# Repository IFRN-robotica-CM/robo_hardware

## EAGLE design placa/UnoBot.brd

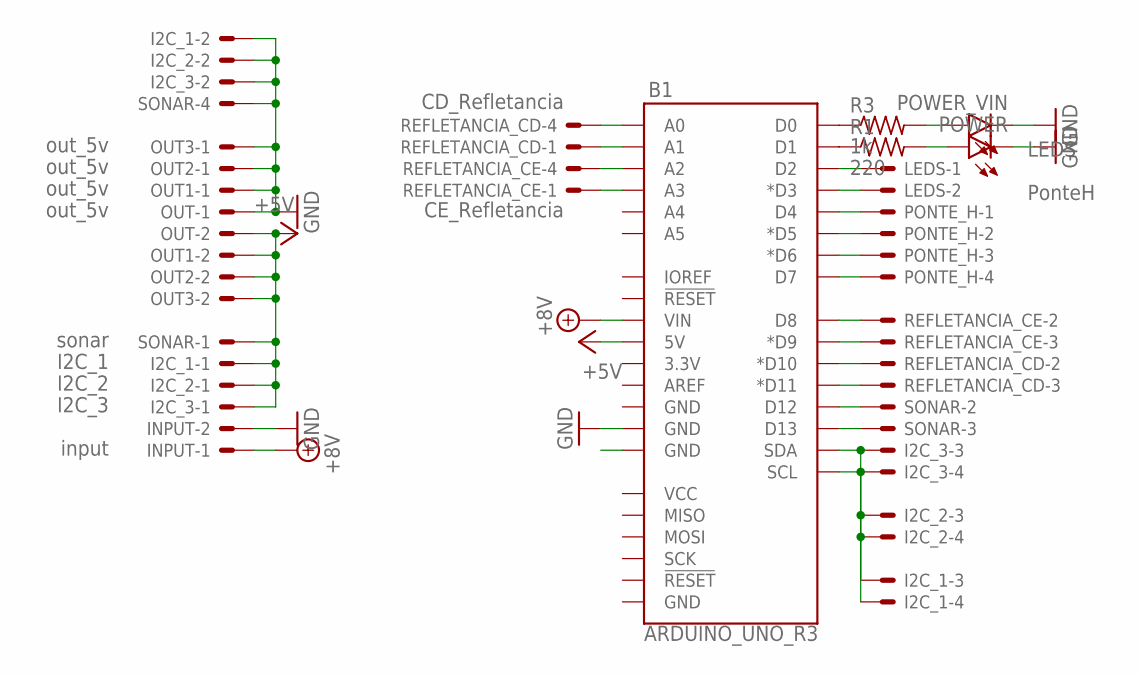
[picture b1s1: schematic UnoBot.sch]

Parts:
B1: ARDUINO_UNO_R3; ARDUINO_R3
I2C_1: I2C_1; JST-XH-04-PACKAGE-LONG-PAD
I2C_2: I2C_2; JST-XH-04-PACKAGE-LONG-PAD
I2C_3: I2C_3; JST-XH-04-PACKAGE-LONG-PAD
INPUT: input; JST-XH-02-PACKAGE-LONG-PAD
LEDS: LEDS; JST-XH-02-PACKAGE-LONG-PAD
OUT, OUT1, OUT2, OUT3: out_5v; JST-XH-02-PACKAGE-LONG-PAD
PONTE_H: PonteH; JST-XH-04-PACKAGE-LONG-PAD
POWER: LEDLED5MM_LONG_PAD; LED5MM_LONG_PAD
POWER_VIN: LEDLED5MM_LONG_PAD; LED5MM_LONG_PAD
R1: 220; 0204/7
R3: 1k; 0204/7
REFLETANCIA_CD: CD_Refletancia; JST-XH-04-PACKAGE-LONG-PAD
REFLETANCIA_CE: CE_Refletancia; JST-XH-04-PACKAGE-LONG-PAD
SONAR: sonar; JST-XH-04-PACKAGE-LONG-PAD

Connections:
+5V: B1.5V, I2C_1.1, I2C_2.1, I2C_3.1, OUT.2, OUT1.2, OUT2.2, OUT3.2, SONAR.1
+8V: B1.VIN, INPUT.1
GND: B1.GND@3 (GND), I2C_1.2, I2C_2.2, I2C_3.2, INPUT.2, OUT.1, OUT1.1, OUT2.1, OUT3.1, POWER.K (C), POWER_VIN.K (C), SONAR.4
unnamed: B1.D4, PONTE_H.1
unnamed: B1.D5 (*D5), PONTE_H.2
unnamed: B1.D6 (*D6), PONTE_H.3
unnamed: B1.D7, PONTE_H.4
unnamed: B1.A0, REFLETANCIA_CD.4
unnamed: B1.A1, REFLETANCIA_CD.1
unnamed: B1.A2, REFLETANCIA_CE.4
unnamed: B1.A3, REFLETANCIA_CE.1
unnamed: B1.D8, REFLETANCIA_CE.2
unnamed: B1.D9 (*D9), REFLETANCIA_CE.3
unnamed: B1.D10 (*D10), REFLETANCIA_CD.2
unnamed: B1.D11 (*D11), REFLETANCIA_CD.3
unnamed: B1.D13, SONAR.3
unnamed: B1.SDA, I2C_1.3, I2C_2.3, I2C_3.3
unnamed: B1.D12, SONAR.2
unnamed: B1.SCL, I2C_1.4, I2C_2.4, I2C_3.4
unnamed: B1.D2, LEDS.1
unnamed: B1.D3 (*D3), LEDS.2
unnamed: B1.D1, R1.1
unnamed: B1.D0, R3.1
unnamed: POWER_VIN.A, R3.2
unnamed: POWER.A, R1.2

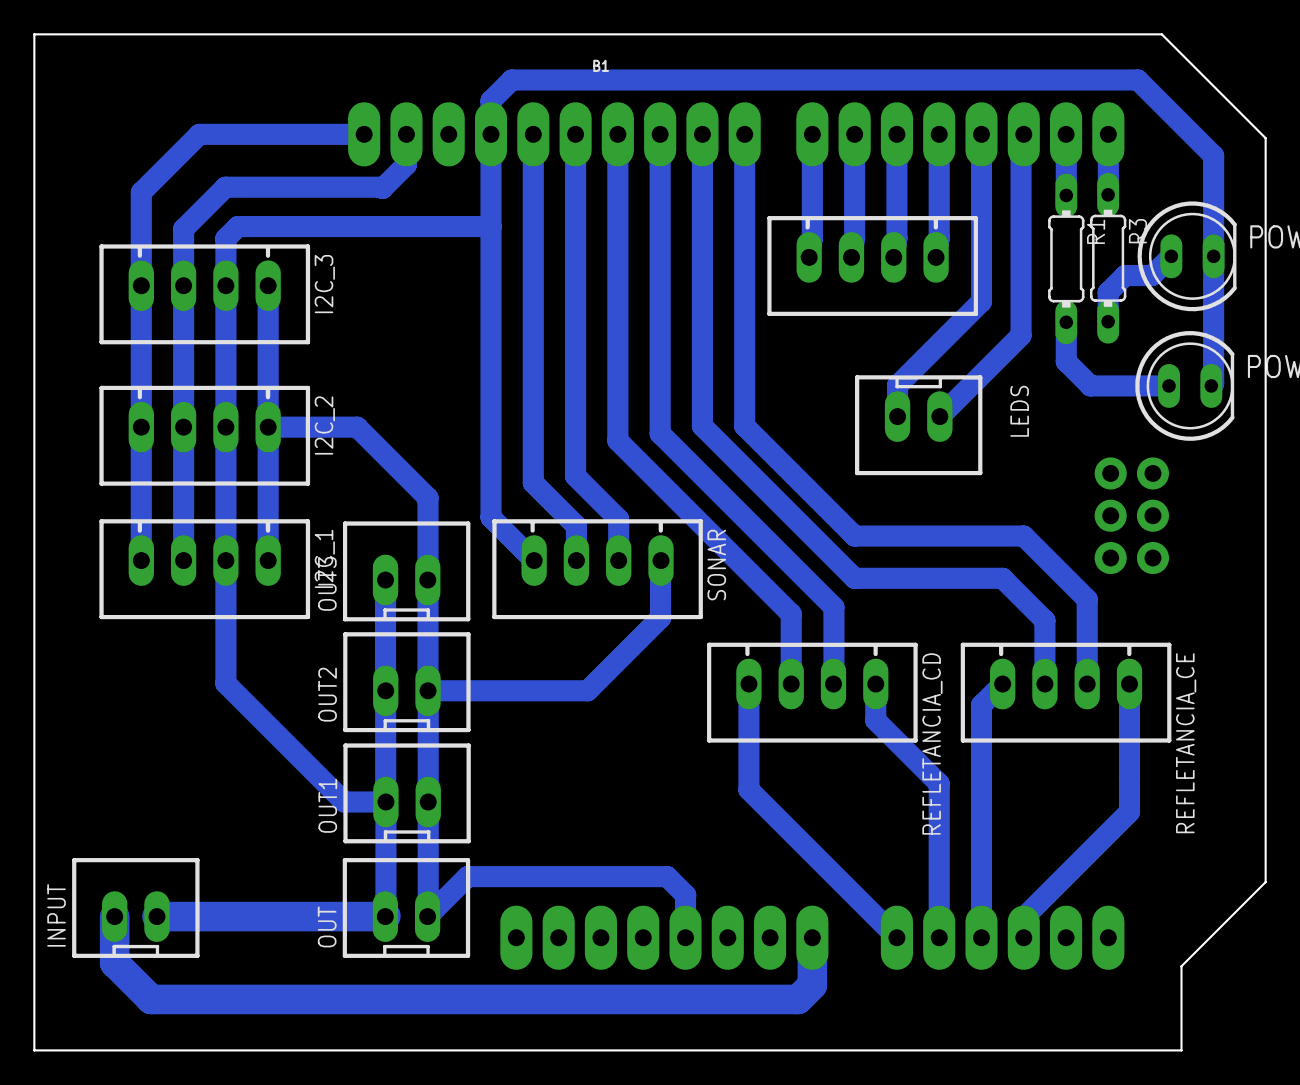
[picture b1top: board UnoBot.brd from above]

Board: 2 copper layers, 74.0 x 61.0 mm, 18 parts (0 on the bottom side), 25 nets.

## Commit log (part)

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2024-02-21 adição sensores de refletância
    foi criado novas funções para leitura dos sensores de refletância frontal e central. foi adicionado pinos para os sensores e leds.
2024-02-21 Adição de novo exemplo
    foi adicionado um exemplo para leitura dos valores dos sensores de refletância central e frontal.
2024-02-21 adição de funções sem ruido
    foi adicionado funções para fazer a leitura dos sensores de refletância central e frontal sem ruido
2024-02-27 remoção de bug
    Atualização da biblioteca Adafruit_TCS34725.h para a versão mais recente. Essa modificação removeu o bug que impedia que a biblioteca lesse os sensores TCS34725 de cor roxa.
2024-02-29 Pinagem do gambiarra
2024-09-12 Criação da biblioteca para o unobot
    Simplificação de várias funcionalidades para casar com a configuração do UNOBOT
2024-10-14 Adição da versão mais atualizada da placa Unobot
    foi adiciona dos arquivos da placa shild unobot
2024-10-14 Correção da pinagem para placa shild unobot
2024-10-14 Organização dos exemplos e funções
2024-10-22 Criação das funções para controle dos leds embarcados na shield megabot
2024-10-24 prinagem dos sensores de refletancia com ruido
2024-10-25 Adição dos arquivos da placa shield Megabot
2024-11-04 sensor de cor com soft i2c
2024-11-25 funções de leitura sensor tcs34725 com soft I2C
2024-11-26 adição de funções para o sensor laiser
2024-11-26 resolvendo problemas de instancia no sensor laiser
2025-04-22 Foi criado funções de leitura dos sensores frontal e central de refletância
2025-05-05 criando função para "leitura tradicional" do sensor de cor (sem o soft I2c)
2025-05-05 leitura dos sensores de cor com multiplexador de I2C
2025-05-09 leitura sensor laser com multiplexador
2025-05-09 remoção bug delay refletância
2025-07-23 Inicio da integração com a garra
2025-08-28 [200~Removes the servo motor related code. This includes removing the servo motor definitions, configurations, and related functions.
2025-09-20 Criação do library.properties para teste se realmente será feita toda a das bibliotecas.
2025-11-26 diponibilização dos valores normatizados em funções e criação de exemplos para acesso das mesmas

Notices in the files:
parts and their libraries:
SparkFun-Boards: Licensing: Creative Commons ShareAlike 4.0 International - https://creativecommons.org/licenses/by-sa/4.0
